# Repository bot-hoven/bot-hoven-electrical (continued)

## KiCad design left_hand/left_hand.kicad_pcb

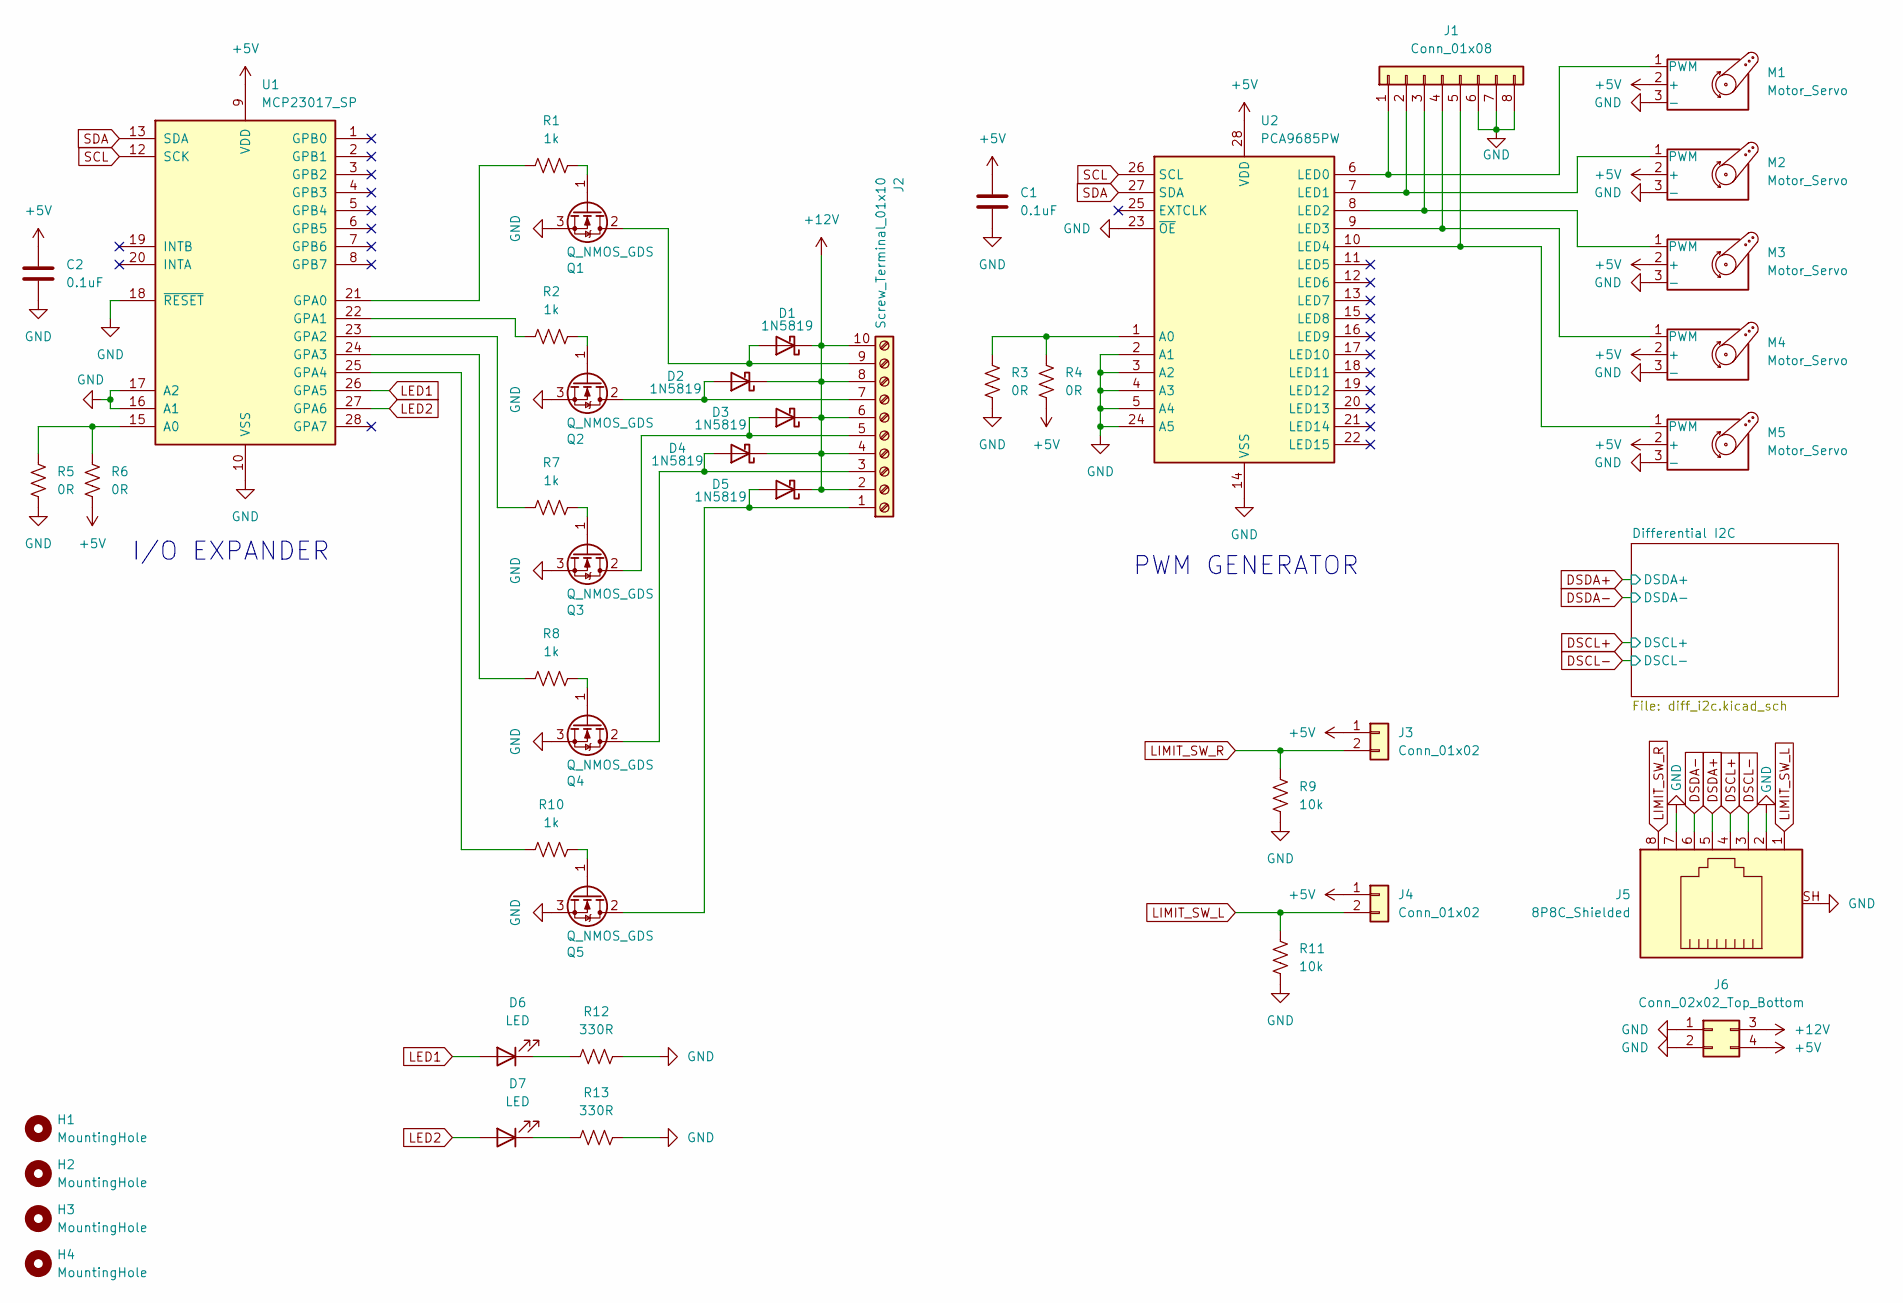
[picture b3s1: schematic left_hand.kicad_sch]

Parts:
C1, C2: 0.1uF; C_Disc_D3.4mm_W2.1mm_P2.50mm
D1, D2, D3, D4, D5: 1N5819; D_DO-41_SOD81_P10.16mm_Horizontal
D6, D7: LED; LED_D5.0mm_Clear
H1, H2, H3, H4: MountingHole; MountingHole_3.2mm_M3
J1: Conn_01x08; PinHeader_1x08_P2.54mm_Vertical
J2: Screw_Terminal_01x10; TerminalBlock_Phoenix_PT-1,5-10-5.0-H_1x10_P5.00mm_Horizont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
J3, J4: Conn_01x02; JST_XH_S2B-XH-A_1x02_P2.50mm_Horizontal
J5: 8P8C_Shielded; RJ45_Amphenol_54602-x08_Horizontal
J6: Conn_02x02_Top_Bottom; Molex_Mini-Fit_Jr_5569-04A2_2x02_P4.20mm_Horizontal
M1, M2, M3, M4, M5: Motor_Servo; PinHeader_1x03_P2.54mm_Vertical
Q1, Q2, Q3, Q4, Q5: Q_NMOS_GDS; TO-220-3_Vertical
R1, R2, R7, R8, R10: 1k; R_Axial_DIN0207_L6.3mm_D2.5mm_P10.16mm_Horizontal
R3, R4, R5, R6: 0R; R_Axial_DIN0207_L6.3mm_D2.5mm_P10.16mm_Horizontal
R9, R11: 10k; R_Axial_DIN0207_L6.3mm_D2.5mm_P10.16mm_Horizontal
R12, R13: 330R; R_Axial_DIN0207_L6.3mm_D2.5mm_P10.16mm_Horizontal
U1: MCP23017_SP; DIP-28_W7.62mm
U2: PCA9685PW; TSSOP-28_4.4x9.7mm_P0.65mm

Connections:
+5V: C1.1, C2.1, J3.1, J4.1, J6.4, M1.2 (+), M2.2 (+), M3.2 (+), M4.2 (+), M5.2 (+), R4.2, R6.2, U1.9 (VDD), U2.28 (VDD); also elsewhere on the board
+12V: D1.1 (K), D2.1 (K), D3.1 (K), D4.1 (K), D5.1 (K), J2.2, J2.4, J2.6, J2.8, J2.10, J6.3
DSCL+: J5.4; also elsewhere on the board
DSCL-: J5.3; also elsewhere on the board
DSDA+: J5.5; also elsewhere on the board
DSDA-: J5.6; also elsewhere on the board
GND: C1.2, C2.2, J1.6, J1.7, J1.8, J5.2, J5.7, J5.SH, J6.1, J6.2, M1.3 (-), M2.3 (-), M3.3 (-), M4.3 (-), M5.3 (-), Q1.3 (S), Q2.3 (S), Q3.3 (S), Q4.3 (S), Q5.3 (S), R3.2, R5.2, R9.1, R11.1, R12.2, R13.2, U1.10 (VSS), U1.16 (A1), U1.17 (A2), U1.18 (~RESET), U2.2 (A1), U2.3 (A2), U2.4 (A3), U2.5 (A4), U2.14 (VSS), U2.23 (~OE), U2.24 (A5); also elsewhere on the board
LED1: D6.2 (A), U1.26 (GPA5)
LED2: D7.2 (A), U1.27 (GPA6)
LIMIT_SW_L: J4.2, J5.1, R11.2
LIMIT_SW_R: J3.2, J5.8, R9.2
unnamed: D1.2 (A), J2.9, Q1.2 (D)
unnamed: D2.2 (A), J2.7, Q2.2 (D)
unnamed: D3.2 (A), J2.5, Q3.2 (D)
unnamed: D4.2 (A), J2.3, Q4.2 (D)
unnamed: D5.2 (A), J2.1, Q5.2 (D)
unnamed: D6.1 (K), R12.1
unnamed: D7.1 (K), R13.1
unnamed: J1.1, M1.1 (PWM), U2.6 (LED0)
unnamed: J1.2, M2.1 (PWM), U2.7 (LED1)
unnamed: J1.3, M3.1 (PWM), U2.8 (LED2)
unnamed: J1.4, M4.1 (PWM), U2.9 (LED3)
unnamed: J1.5, M5.1 (PWM), U2.10 (LED4)
unnamed: Q1.1 (G), R1.2
unnamed: Q2.1 (G), R2.2
unnamed: Q3.1 (G), R7.2
unnamed: Q4.1 (G), R8.2
unnamed: Q5.1 (G), R10.2
unnamed: R5.1, R6.1, U1.15 (A0)
unnamed: R1.1, U1.21 (GPA0)
unnamed: R2.1, U1.22 (GPA1)
unnamed: R7.1, U1.23 (GPA2)
unnamed: R8.1, U1.24 (GPA3)
unnamed: R10.1, U1.25 (GPA4)
unnamed: R3.1, R4.1, U2.1 (A0)
SCL: U1.12 (SCK), U2.26 (SCL); also elsewhere on the board
SDA: U1.13 (SDA), U2.27 (SDA); also elsewhere on the board

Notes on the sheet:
PWM GENERATOR
I/O EXPANDER

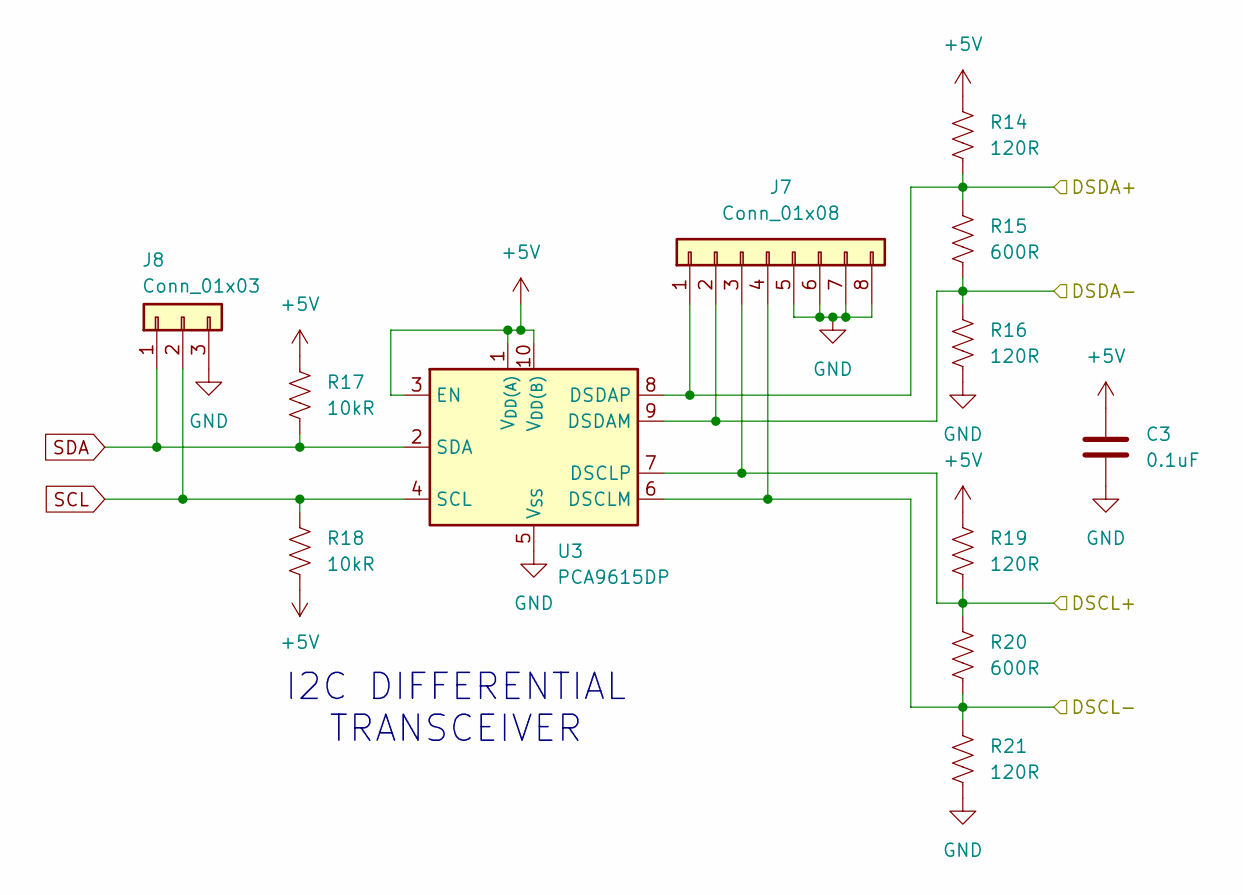
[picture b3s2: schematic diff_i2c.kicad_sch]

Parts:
C3: 0.1uF; C_Disc_D3.4mm_W2.1mm_P2.50mm
J7: Conn_01x08; PinHeader_1x08_P2.54mm_Vertical
J8: Conn_01x03; PinHeader_1x03_P2.54mm_Vertical
R14, R16, R19, R21: 120R; R_Axial_DIN0207_L6.3mm_D2.5mm_P10.16mm_Horizontal
R15, R20: 600R; R_Axial_DIN0207_L6.3mm_D2.5mm_P10.16mm_Horizontal
R17, R18: 10kR; R_Axial_DIN0207_L6.3mm_D2.5mm_P10.16mm_Horizontal
U3: PCA9615DP; TSSOP-10_3x3mm_P0.5mm

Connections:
+5V: C3.1, R14.1, R17.1, R18.2, R19.1, U3.1 (V_{DD(A)}), U3.3 (EN), U3.10 (V_{DD(B)}); also elsewhere on the board
DSCL+: J7.3, R19.2, R20.1, U3.7 (DSCLP); also elsewhere on the board
DSCL-: J7.4, R20.2, R21.1, U3.6 (DSCLM); also elsewhere on the board
DSDA+: J7.1, R14.2, R15.1, U3.8 (DSDAP); also elsewhere on the board
DSDA-: J7.2, R15.2, R16.1, U3.9 (DSDAM); also elsewhere on the board
GND: C3.2, J7.5, J7.6, J7.7, J7.8, J8.3, R16.2, R21.2, U3.5 (V_{SS}); also elsewhere on the board
SCL: J8.2, R18.1, U3.4 (SCL); also elsewhere on the board
SDA: J8.1, R17.2, U3.2 (SDA); also elsewhere on the board

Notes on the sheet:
I2C DIFFERENTIAL TRANSCEIVER

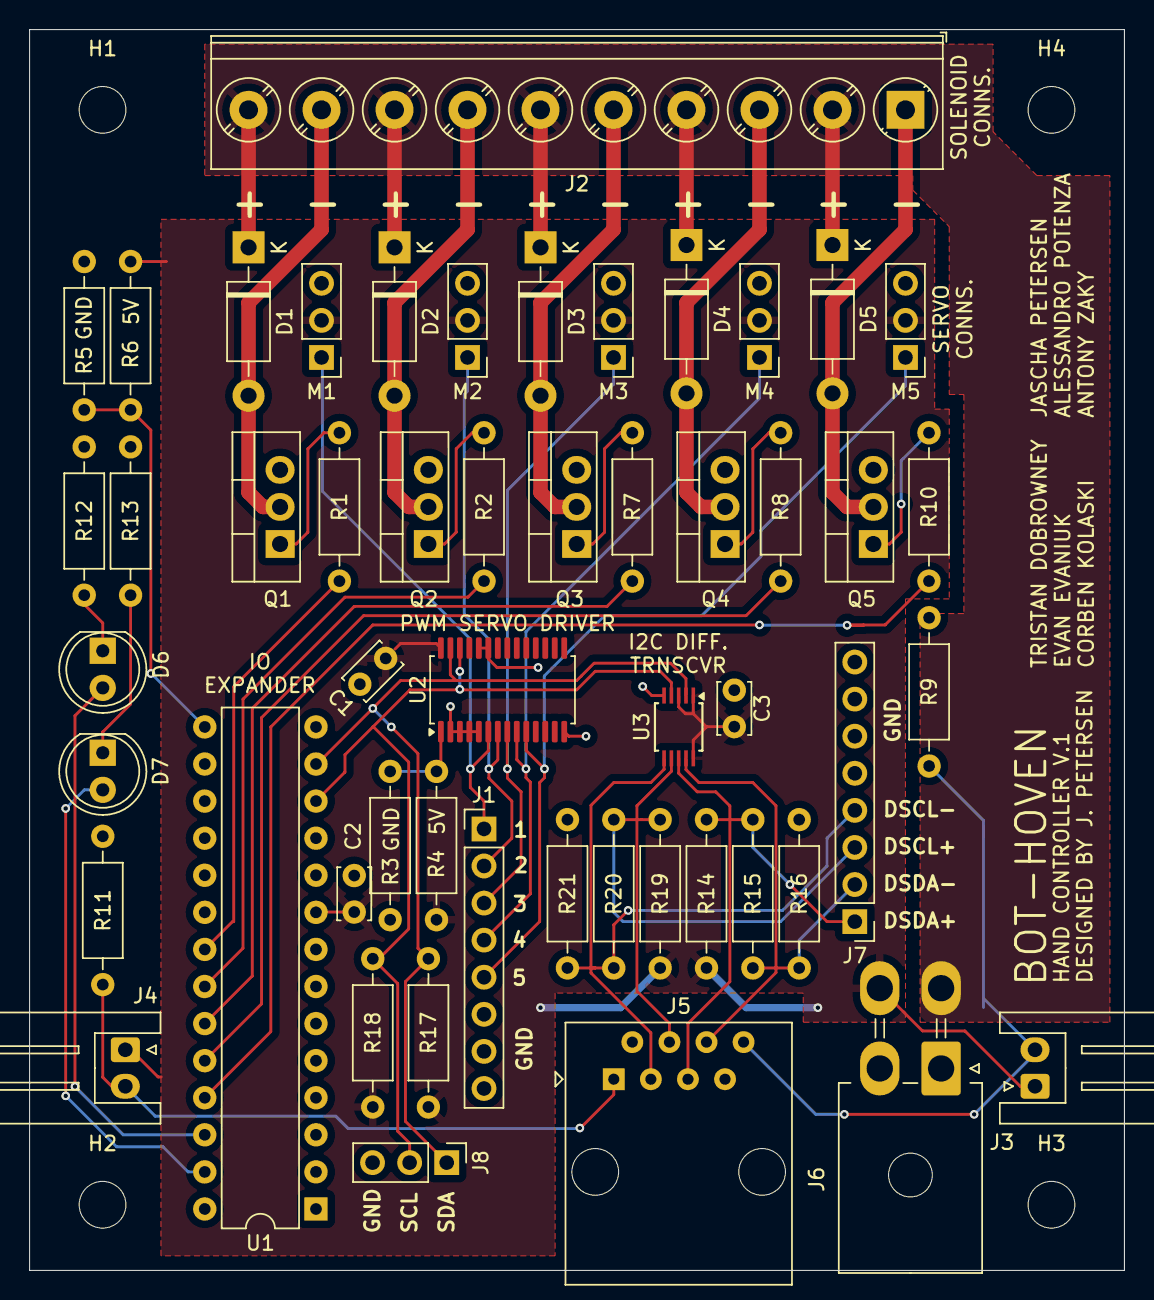
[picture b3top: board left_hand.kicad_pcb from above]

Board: 2 copper layers, 75.0 x 85.0 mm, 56 parts (0 on the bottom side), 37 nets.

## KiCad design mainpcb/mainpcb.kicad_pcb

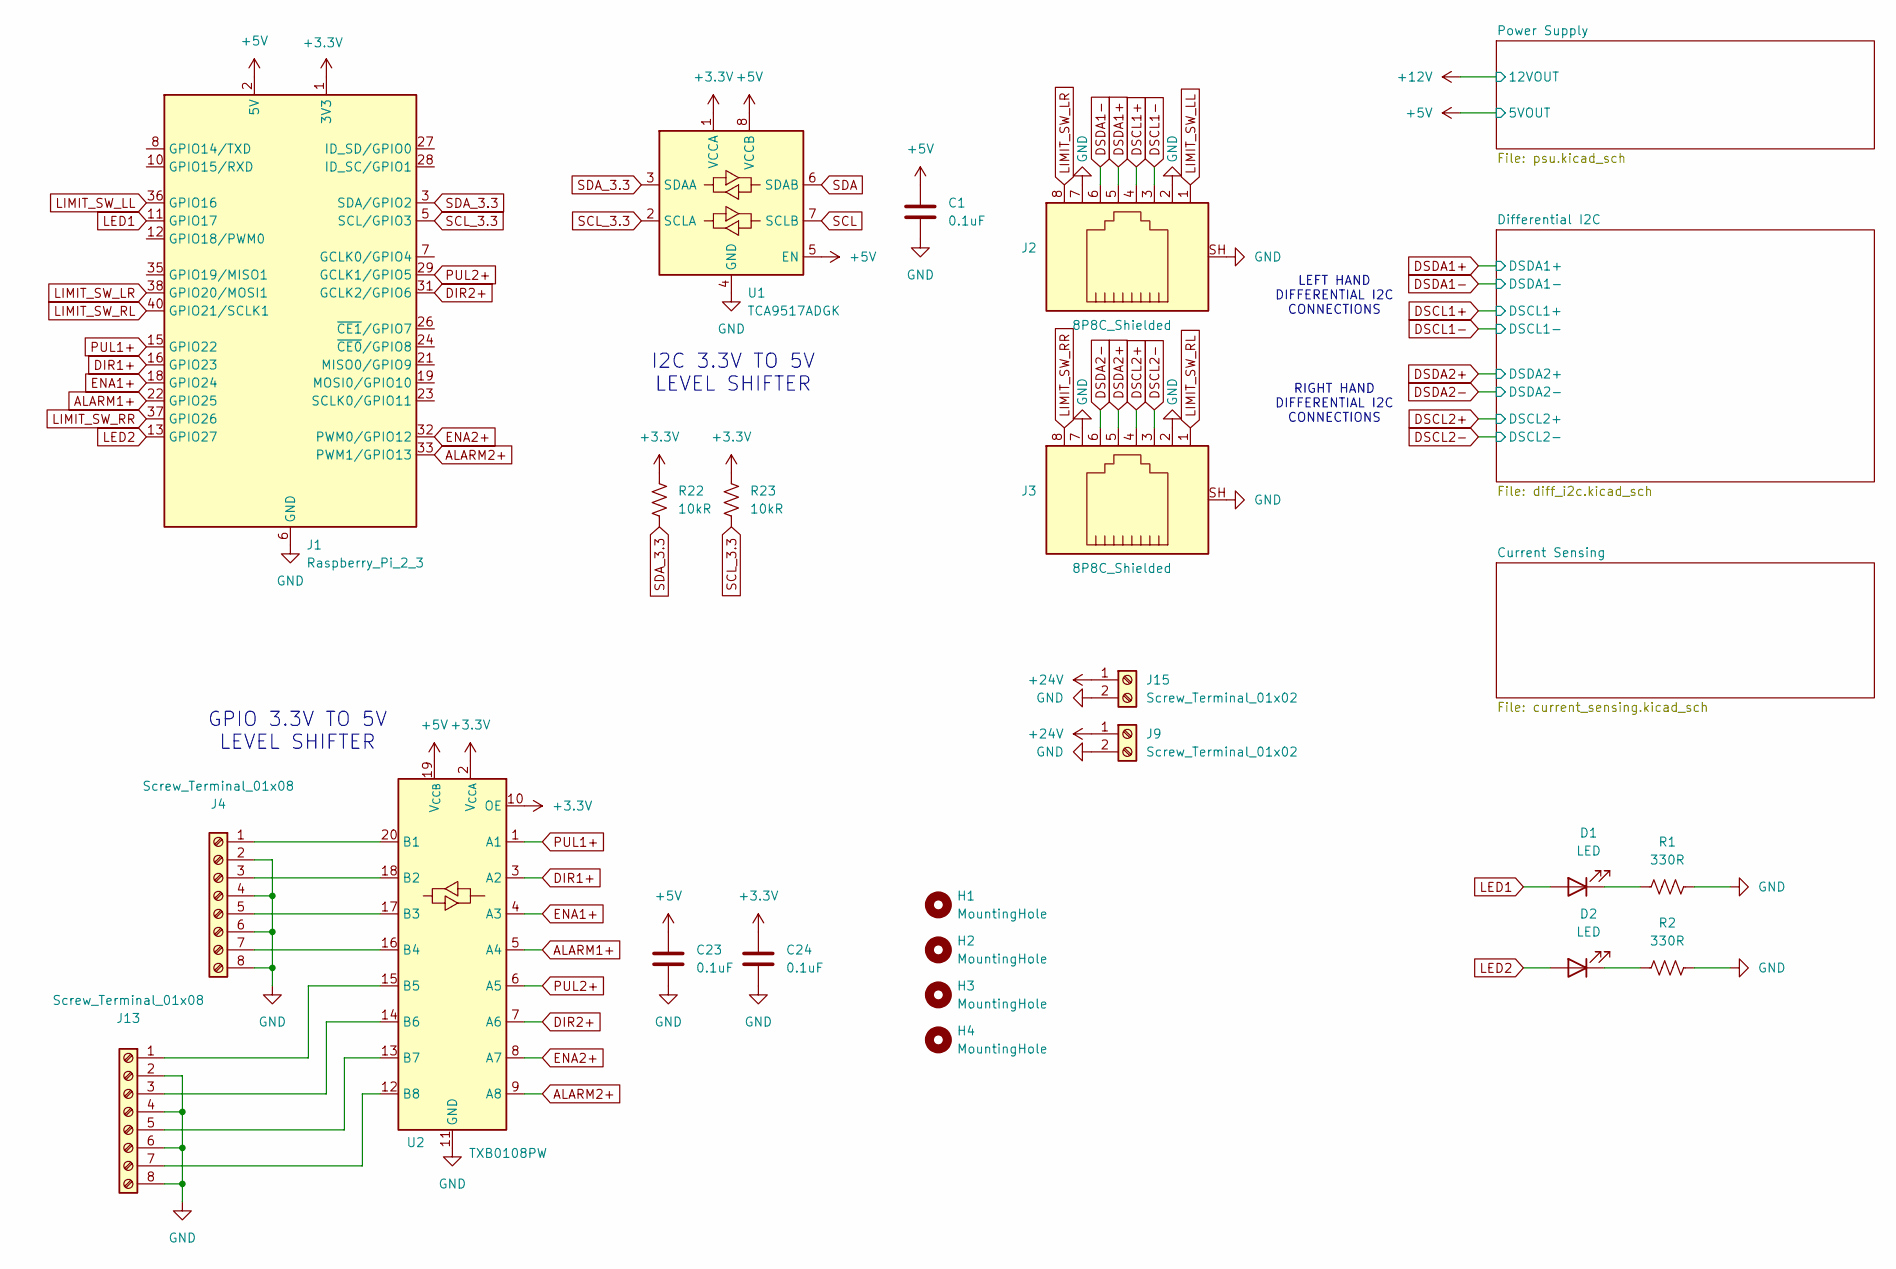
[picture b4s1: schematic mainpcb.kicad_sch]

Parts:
C1, C23, C24: 0.1uF; C_Rect_L4.6mm_W2.0mm_P2.50mm_MKS02_FKP02
D1, D2: LED; LED_D5.0mm_Clear
H1, H2, H3, H4: MountingHole; MountingHole_4.3mm_M4
J1: Raspberry_Pi_2_3; PinHeader_2x20_P2.54mm_Vertical
J2, J3: 8P8C_Shielded; RJ45_Amphenol_54602-x08_Horizontal
J4, J13: Screw_Terminal_01x08; TerminalBlock_Phoenix_PT-1,5-8-5.0-H_1x08_P5.00mm_Horizontal
J9, J15: Screw_Terminal_01x02; TerminalBlock_Phoenix_PT-1,5-2-5.0-H_1x02_P5.00mm_Horizontal
R1, R2: 330R; R_Axial_DIN0207_L6.3mm_D2.5mm_P10.16mm_Horizontal
R22, R23: 10kR; R_Axial_DIN0207_L6.3mm_D2.5mm_P10.16mm_Horizontal
U1: TCA9517ADGK; VSSOP-8_3x3mm_P0.65mm
U2: TXB0108PW; TSSOP-20_4.4x6.5mm_P0.65mm

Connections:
+3.3V: C24.1, J1.1 (3V3), J1.17 (3V3), R22.1, R23.1, U1.1 (VCCA), U2.2 (V_{CCA}), U2.10 (OE)
+5V: C1.1, C23.1, J1.2 (5V), J1.4 (5V), U1.5 (EN), U1.8 (VCCB), U2.19 (V_{CCB}); also elsewhere on the board
+24V: J9.1, J15.1; also elsewhere on the board
ALARM1+: J1.22 (GPIO25), U2.5 (A4)
ALARM2+: J1.33 (PWM1/GPIO13), U2.9 (A8)
DIR1+: J1.16 (GPIO23), U2.3 (A2)
DIR2+: J1.31 (GCLK2/GPIO6), U2.7 (A6)
DSCL1+: J2.4; also elsewhere on the board
DSCL1-: J2.3; also elsewhere on the board
DSCL2+: J3.4; also elsewhere on the board
DSCL2-: J3.3; also elsewhere on the board
DSDA1+: J2.5; also elsewhere on the board
DSDA1-: J2.6; also elsewhere on the board
DSDA2+: J3.5; also elsewhere on the board
DSDA2-: J3.6; also elsewhere on the board
ENA1+: J1.18 (GPIO24), U2.4 (A3)
ENA2+: J1.32 (PWM0/GPIO12), U2.8 (A7)
GND: C1.2, C23.2, C24.2, J1.6 (GND), J1.9 (GND), J1.14 (GND), J1.20 (GND), J1.25 (GND), J1.30 (GND), J1.34 (GND), J1.39 (GND), J2.2, J2.7, J2.SH, J3.2, J3.7, J3.SH, J4.2, J4.4, J4.6, J4.8, J9.2, J13.2, J13.4, J13.6, J13.8, J15.2, R1.2, R2.2, U1.4 (GND), U2.11 (GND); also elsewhere on the board
LED1: D1.2 (A), J1.11 (GPIO17)
LED2: D2.2 (A), J1.13 (GPIO27)
LIMIT_SW_LL: J1.36 (GPIO16), J2.1
LIMIT_SW_LR: J1.38 (GPIO20/MOSI1), J2.8
LIMIT_SW_RL: J1.40 (GPIO21/SCLK1), J3.1
LIMIT_SW_RR: J1.37 (GPIO26), J3.8
unnamed: D1.1 (K), R1.1
unnamed: D2.1 (K), R2.1
unnamed: J4.1, U2.20 (B1)
unnamed: J4.3, U2.18 (B2)
unnamed: J4.5, U2.17 (B3)
unnamed: J4.7, U2.16 (B4)
unnamed: J13.1, U2.15 (B5)
unnamed: J13.3, U2.14 (B6)
unnamed: J13.5, U2.13 (B7)
unnamed: J13.7, U2.12 (B8)
PUL1+: J1.15 (GPIO22), U2.1 (A1)
PUL2+: J1.29 (GCLK1/GPIO5), U2.6 (A5)
SCL: U1.7 (SCLB); also elsewhere on the board
SCL_3.3: J1.5 (SCL/GPIO3), R23.2, U1.2 (SCLA)
SDA: U1.6 (SDAB); also elsewhere on the board
SDA_3.3: J1.3 (SDA/GPIO2), R22.2, U1.3 (SDAA)

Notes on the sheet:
I2C 3.3V TO 5V LEVEL SHIFTER
RIGHT HAND DIFFERENTIAL I2C CONNECTIONS
LEFT HAND DIFFERENTIAL I2C CONNECTIONS
GPIO 3.3V TO 5V LEVEL SHIFTER

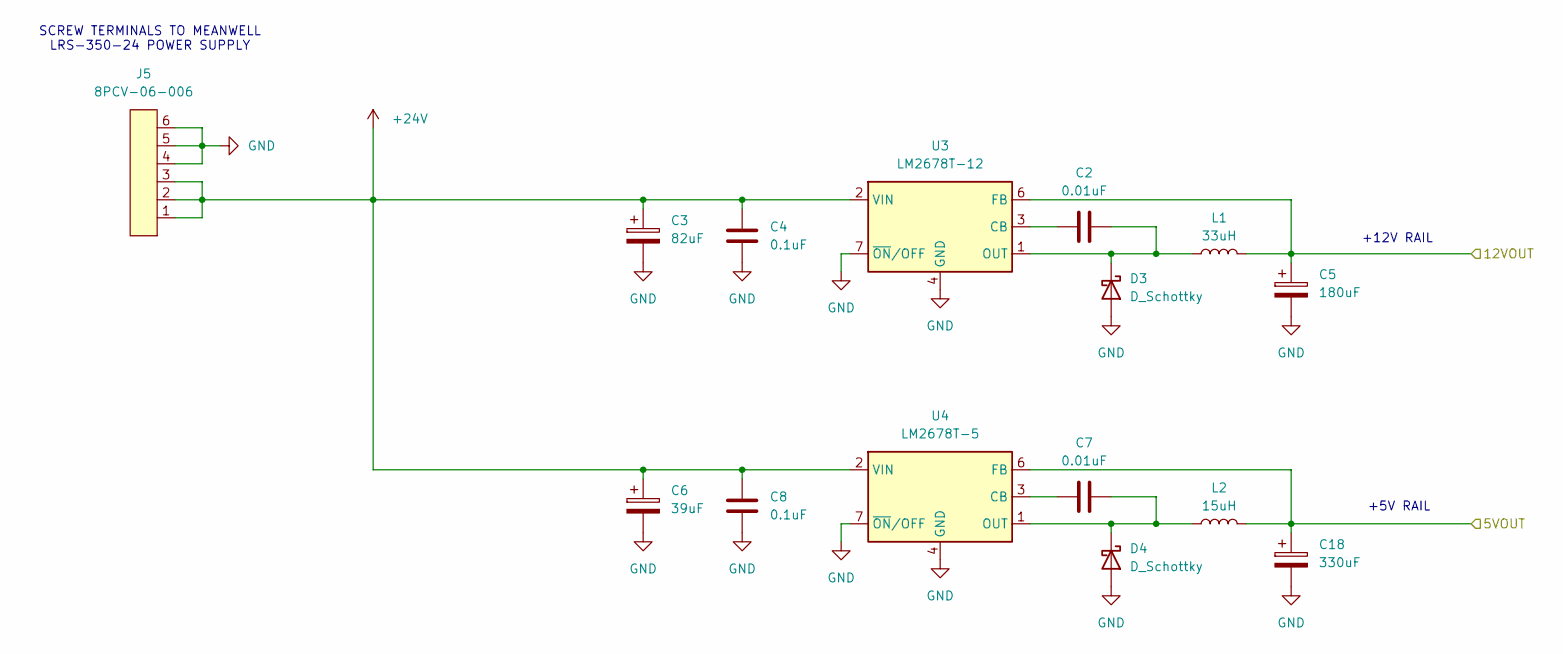
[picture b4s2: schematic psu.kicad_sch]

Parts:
C2, C7: 0.01uF; C_Rect_L4.0mm_W2.5mm_P2.50mm
C3: 82uF; CP_Radial_D8.0mm_P3.50mm
C4, C8: 0.1uF; C_Rect_L4.0mm_W2.5mm_P2.50mm
C5: 180uF; CP_Radial_D8.0mm_P3.50mm
C6: 39uF; CP_Radial_D8.0mm_P3.50mm
C18: 330uF; C_Radial_D10.0mm_H12.5mm_P5.00mm
D3, D4: D_Schottky; D_DO-27_P15.24mm_Horizontal
J5: 8PCV-06-006; Terminal_Block_8PCV-06-006
L1: 33uH; L_Toroid_Vertical_L31.8mm_W15.9mm_P13.50mm_Bourns_5700
L2: 15uH; L_Toroid_Vertical_L31.8mm_W15.9mm_P13.50mm_Bourns_5700
U3: LM2678T-12; TO-220-7_P2.54x3.7mm_StaggerOdd_Lead3.8mm_Vertical
U4: LM2678T-5; TO-220-7_P2.54x3.7mm_StaggerOdd_Lead3.8mm_Vertical

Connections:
+5V: C18.1, L2.2, U4.6 (FB); also elsewhere on the board
+12V: C5.1, L1.2, U3.6 (FB); also elsewhere on the board
+24V: C3.1, C4.1, C6.1, C8.1, J5.1, J5.2, J5.3, U3.2 (VIN), U4.2 (VIN); also elsewhere on the board
GND: C3.2, C4.2, C5.2, C6.2, C8.2, C18.2, D3.2 (A), D4.2 (A), J5.4, J5.5, J5.6, U3.4 (GND), U3.7 (~ON/OFF), U4.4 (GND), U4.7 (~ON/OFF); also elsewhere on the board
unnamed: C2.2, D3.1 (K), L1.1, U3.1 (OUT)
unnamed: C7.2, D4.1 (K), L2.1, U4.1 (OUT)
unnamed: C2.1, U3.3 (CB)
unnamed: C7.1, U4.3 (CB)

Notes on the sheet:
SCREW TERMINALS TO MEANWELL LRS-350-24 POWER SUPPLY
+12V RAIL
+5V RAIL

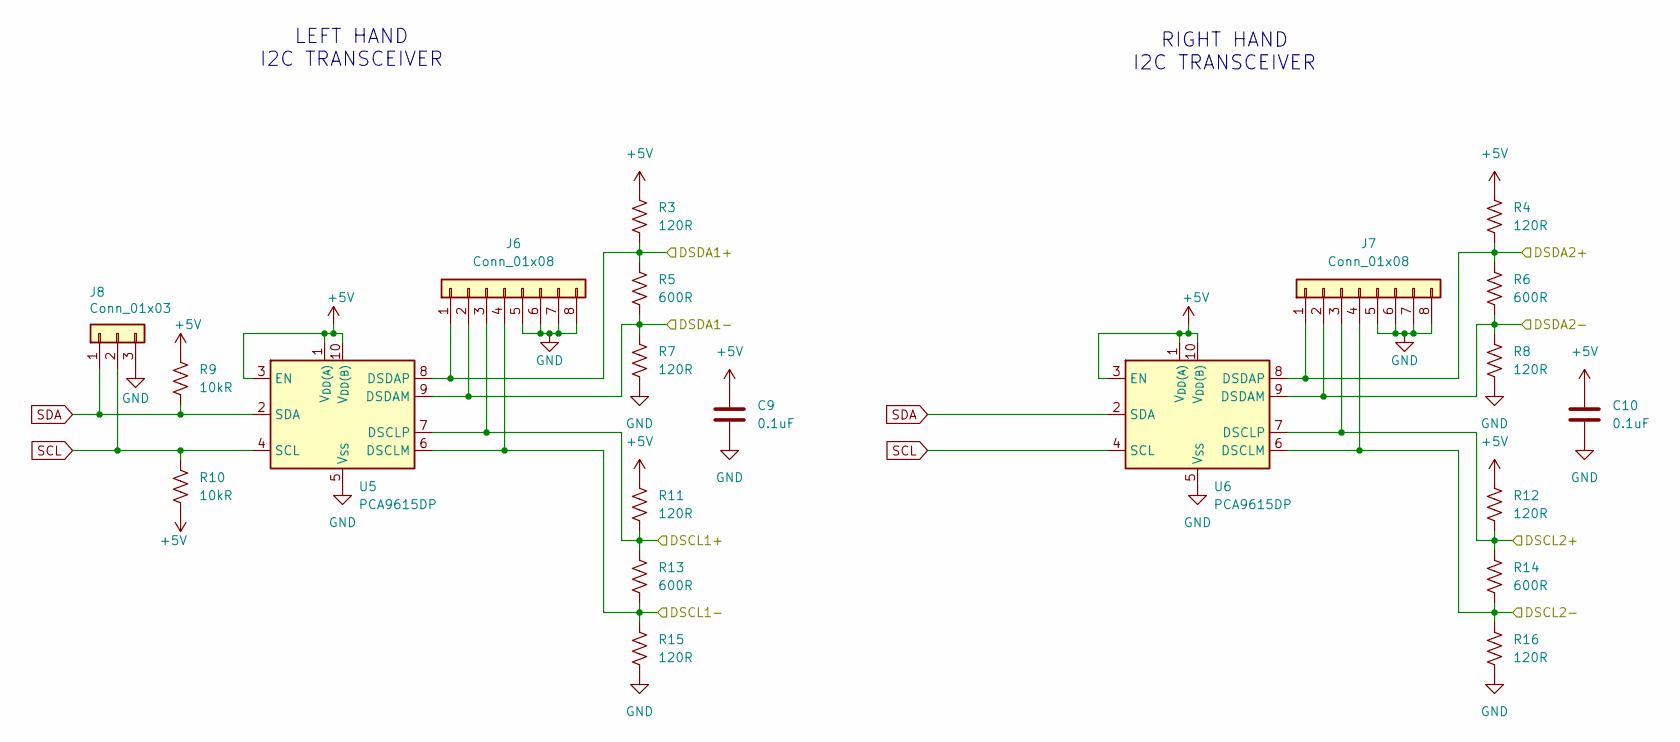
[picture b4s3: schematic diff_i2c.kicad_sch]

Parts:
C9, C10: 0.1uF; C_Rect_L4.6mm_W2.0mm_P2.50mm_MKS02_FKP02
J6, J7: Conn_01x08; PinHeader_1x08_P2.54mm_Vertical
J8: Conn_01x03; PinHeader_1x03_P2.54mm_Vertical
R3, R4, R7, R8, R11, R12, R15, R16: 120R; R_Axial_DIN0207_L6.3mm_D2.5mm_P10.16mm_Horizontal
R5, R6, R13, R14: 600R; R_Axial_DIN0207_L6.3mm_D2.5mm_P10.16mm_Horizontal
R9, R10: 10kR; R_Axial_DIN0207_L6.3mm_D2.5mm_P10.16mm_Horizontal
U5, U6: PCA9615DP; TSSOP-10_3x3mm_P0.5mm

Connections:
+5V: C9.1, C10.1, R3.1, R4.1, R9.1, R10.2, R11.1, R12.1, U5.1 (V_{DD(A)}), U5.3 (EN), U5.10 (V_{DD(B)}), U6.1 (V_{DD(A)}), U6.3 (EN), U6.10 (V_{DD(B)}); also elsewhere on the board
DSCL1+: J6.3, R11.2, R13.1, U5.7 (DSCLP); also elsewhere on the board
DSCL1-: J6.4, R13.2, R15.1, U5.6 (DSCLM); also elsewhere on the board
DSCL2+: J7.3, R12.2, R14.1, U6.7 (DSCLP); also elsewhere on the board
DSCL2-: J7.4, R14.2, R16.1, U6.6 (DSCLM); also elsewhere on the board
DSDA1+: J6.1, R3.2, R5.1, U5.8 (DSDAP); also elsewhere on the board
DSDA1-: J6.2, R5.2, R7.1, U5.9 (DSDAM); also elsewhere on the board
DSDA2+: J7.1, R4.2, R6.1, U6.8 (DSDAP); also elsewhere on the board
DSDA2-: J7.2, R6.2, R8.1, U6.9 (DSDAM); also elsewhere on the board
GND: C9.2, C10.2, J6.5, J6.6, J6.7, J6.8, J7.5, J7.6, J7.7, J7.8, J8.3, R7.2, R8.2, R15.2, R16.2, U5.5 (V_{SS}), U6.5 (V_{SS}); also elsewhere on the board
SCL: J8.2, R10.1, U5.4 (SCL), U6.4 (SCL); also elsewhere on the board
SDA: J8.1, R9.2, U5.2 (SDA), U6.2 (SDA); also elsewhere on the board

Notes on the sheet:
LEFT HAND I2C TRANSCEIVER
RIGHT HAND I2C TRANSCEIVER

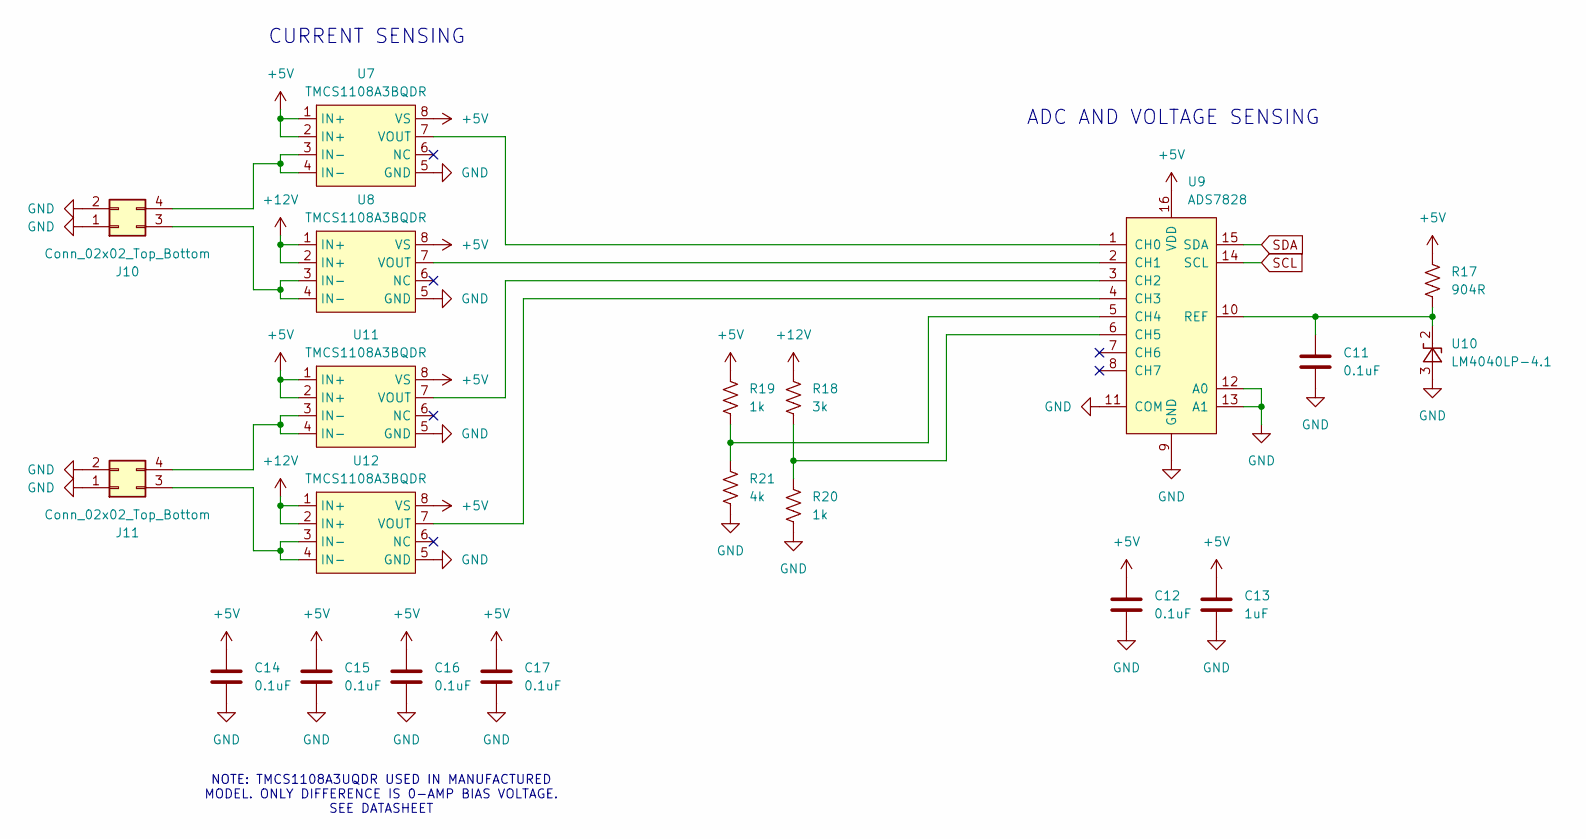
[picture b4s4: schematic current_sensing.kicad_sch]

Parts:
C11, C12, C14, C15, C16, C17: 0.1uF; C_Rect_L4.6mm_W2.0mm_P2.50mm_MKS02_FKP02
C13: 1uF; C_Rect_L4.6mm_W2.0mm_P2.50mm_MKS02_FKP02
J10, J11: Conn_02x02_Top_Bottom; Molex_Mini-Fit_Jr_5569-04A2_2x02_P4.20mm_Horizontal
R17: 904R; R_Axial_DIN0207_L6.3mm_D2.5mm_P10.16mm_Horizontal
R18: 3k; R_Axial_DIN0207_L6.3mm_D2.5mm_P10.16mm_Horizontal
R19, R20: 1k; R_Axial_DIN0207_L6.3mm_D2.5mm_P10.16mm_Horizontal
R21: 4k; R_Axial_DIN0207_L6.3mm_D2.5mm_P10.16mm_Horizontal
U7, U8, U11, U12: TMCS1108A3BQDR; SOIC-8_3.9x4.9mm_P1.27mm
U9: ADS7828; TSSOP-16_4.4x5mm_P0.65mm
U10: LM4040LP-4.1; TO-92_Inline

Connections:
+5V: C12.1, C13.1, C14.1, C15.1, C16.1, C17.1, R17.1, R19.1, U7.1 (IN+), U7.2 (IN+), U7.8 (VS), U8.8 (VS), U9.16 (VDD), U11.1 (IN+), U11.2 (IN+), U11.8 (VS), U12.8 (VS); also elsewhere on the board
+12V: R18.1, U8.1 (IN+), U8.2 (IN+), U12.1 (IN+), U12.2 (IN+); also elsewhere on the board
GND: C11.2, C12.2, C13.2, C14.2, C15.2, C16.2, C17.2, J10.1, J10.2, J11.1, J11.2, R20.2, R21.2, U7.5 (GND), U8.5 (GND), U9.9 (GND), U9.11 (COM), U9.12 (A0), U9.13 (A1), U10.3 (A), U11.5 (GND), U12.5 (GND); also elsewhere on the board
unnamed: J10.3, U8.3 (IN-), U8.4 (IN-)
unnamed: J10.4, U7.3 (IN-), U7.4 (IN-)
unnamed: J11.3, U12.3 (IN-), U12.4 (IN-)
unnamed: J11.4, U11.3 (IN-), U11.4 (IN-)
unnamed: U7.7 (VOUT), U9.1 (CH0)
unnamed: U8.7 (VOUT), U9.2 (CH1)
unnamed: R19.2, R21.1, U9.5 (CH4)
unnamed: R18.2, R20.1, U9.6 (CH5)
unnamed: C11.1, R17.2, U9.10 (REF), U10.2 (K)
unnamed: U9.3 (CH2), U11.7 (VOUT)
unnamed: U9.4 (CH3), U12.7 (VOUT)
SCL: U9.14 (SCL); also elsewhere on the board
SDA: U9.15 (SDA); also elsewhere on the board

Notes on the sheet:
ADC AND VOLTAGE SENSING
CURRENT SENSING
NOTE: TMCS1108A3UQDR USED IN MANUFACTURED MODEL. ONLY DIFFERENCE IS 0-AMP BIAS VOLTAGE. SEE DATASHEET

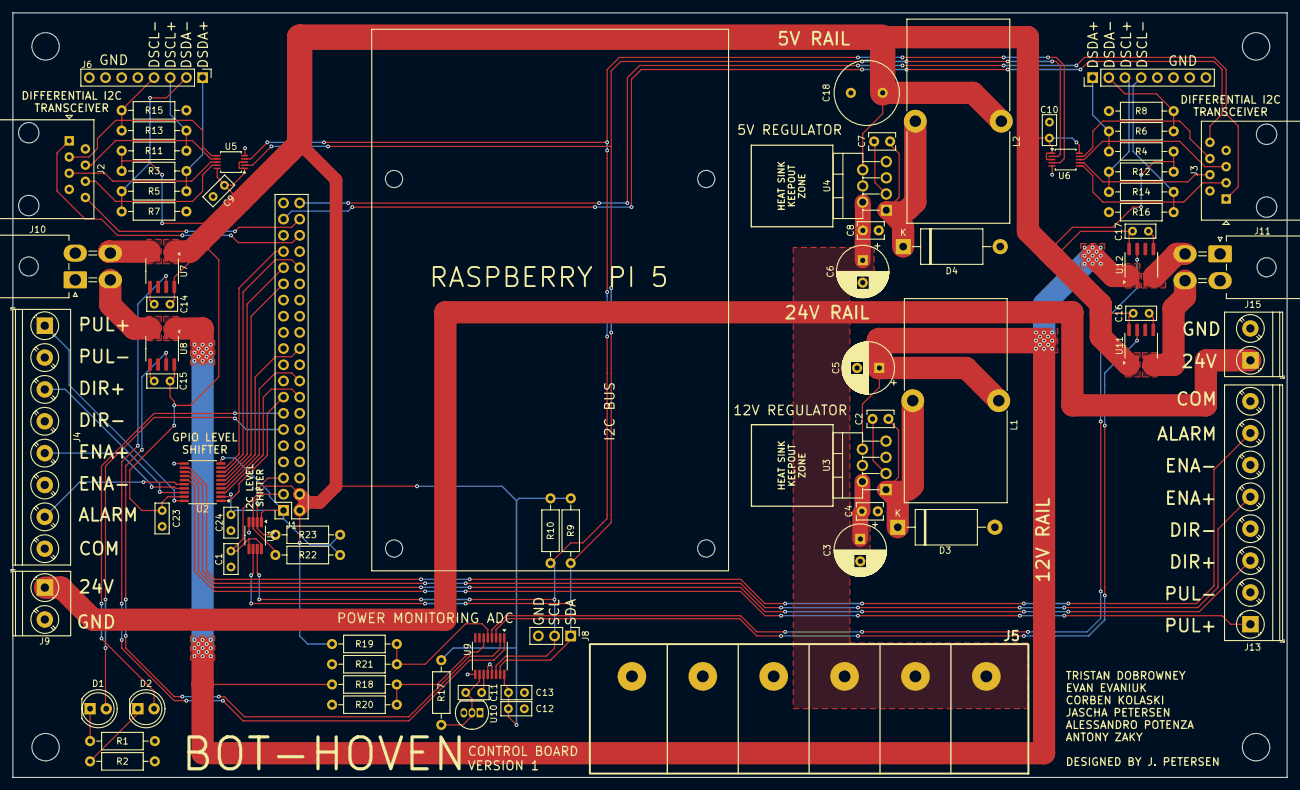
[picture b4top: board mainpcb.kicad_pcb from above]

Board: 2 copper layers, 200.0 x 120.0 mm, 78 parts (0 on the bottom side), 56 nets.

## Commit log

2024-09-24 Added KiCad project
    Basic power supply design is complete
2024-10-06 Added PSU terminal block symbol
    Also created bh_part_library for custom modelled parts used in the bot-hoven project.
2024-10-07 Some hand components, PSU changes
    Updated PSU to 24V rail regulated to 5V and 3.3V. Hopefully we won't need a 12V rail. Made some part selections, added IO expander for hand, mosfet, made solenoid symbol.
2024-10-07 Added PCA9615 differential I2C buffer
2024-10-07 Added PCA9685 PWM generator IC
2024-10-11 Added 12V power rail and regulator
2024-10-11 Created LM2678 12V regulator symbol
    Updated 12V regulator circuit
2024-10-12 Added TCA9517 I2C level shifter
2024-10-15 I2C diff. and single side bus changes
    Added differential termination on each end. Todo: determine maximum differential bias voltage. Added pull up resistors for I2C lines.
    Added decoupling caps.
2024-10-16 Added debug headers to stuff
    Added debug headers to I2C single ended lines and differential lines
2024-11-01 Added ICs
    Added ADC IC
    Switched to schottky flyback diode for better response times
2024-11-08 Added gate resistors to MOSFETs
2024-11-19 I2C transceivers, sheet hierarchy changes
    Added I2C transceivers for both hands on the controller side, also changed sheet hierarchy to modularize controller board sheet somewhat
2024-11-19 Added GPIO level shifter
    Added general purpose TXB0108 level shifter to translate from 3.3V to 5V logic between the RPi and motor driver
    Future connections will be for limit switches etc.
2024-11-19 Tie output enable pin on TXB0108 to 3.3V
2024-11-27 Major update
    Hand PCB mostly complete
2024-11-27 Added current and voltage sensing on control board
2024-12-02 Added limit switches to hand and readme
2024-12-03 Added screw terminals etc for both stepper drivers
2024-12-03 Started layout of control board
2024-12-04 Continued control board layout
2024-12-05 Started signal track layout of control PCB
2024-12-05 Completed control board layout
2024-12-06 As-Produced commit
    This commit contains the PCBs as they were sent to the manufacturer
2025-01-08 Updated differential termination resistor values
2025-01-31 Version 1 AS-BUILT commit
    This commit has the schematics of version 1 of the system AS IT WAS BUILT
2025-01-31 Added drawing information boxes
2025-01-31 Added PDF schematic exports
2025-02-07 Starting hardware version 2
    Created version 2 control board project file
    Added raspberry pi pico symbol and footprint
    Both probably need work but will do for now
    Restructured directories
2025-02-09 Doing stuff
2025-02-09 Added TXU0304 level shifter
    Added unidirectional SPI compatible level shifter
2025-02-09 Preliminary V2 schematics
2025-02-10 Added hand ADCs
    Subject to change without notice
2025-02-11 Replaced hand ADCs with ADS7138
2025-02-15 Doing some things
    Crossing some ts and dotting some is. Making v3 of the BOM.
2025-02-16 Switched logic level shifting from SPI to GPIO
    RPi Pico uses 5V power in but has an internal 3.3V regulator so uses 3.3V logic. Level shifting not required for SPI then but required for GPIO pins going to stepper control outputs
2025-03-02 Doing some things
2025-03-04 Doing more things
2025-03-04 Doing more things 2
2025-03-05 Version 2 As-Ordered commit
    Minor changes to polish things up.
    Version 2 is a major revision from the last revision, version 1. There are now 10 servo channels in addition to the 5 solenoid channels, and ADC feedback for those servos.
